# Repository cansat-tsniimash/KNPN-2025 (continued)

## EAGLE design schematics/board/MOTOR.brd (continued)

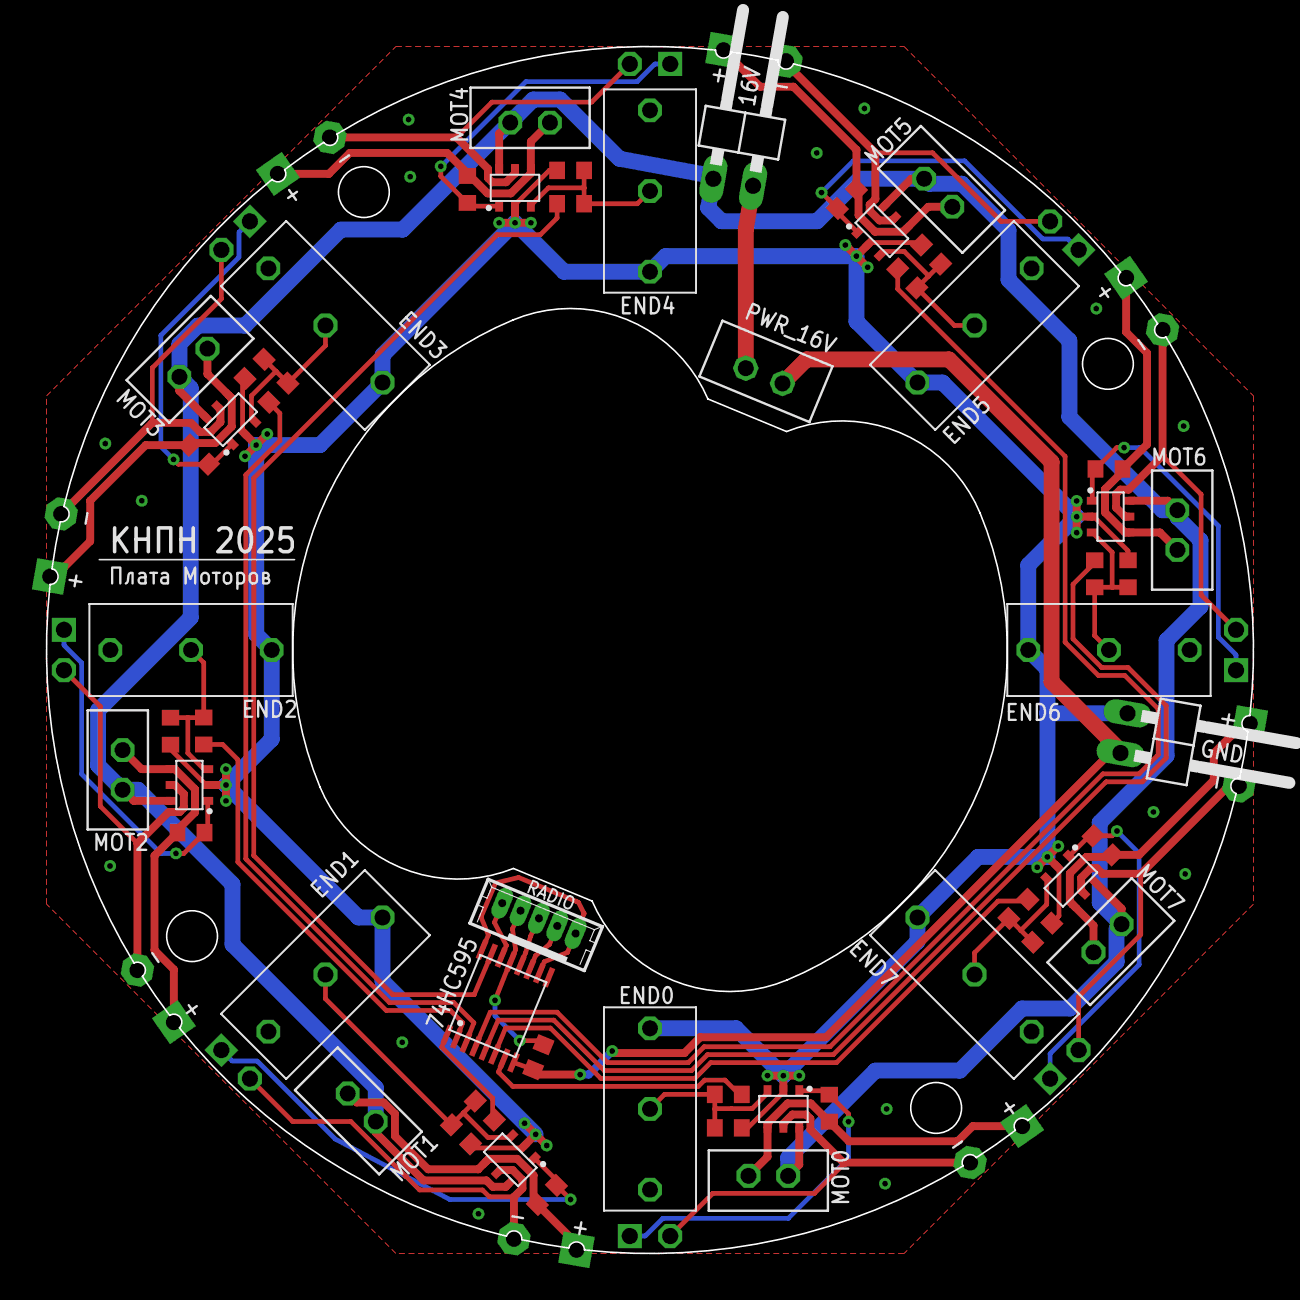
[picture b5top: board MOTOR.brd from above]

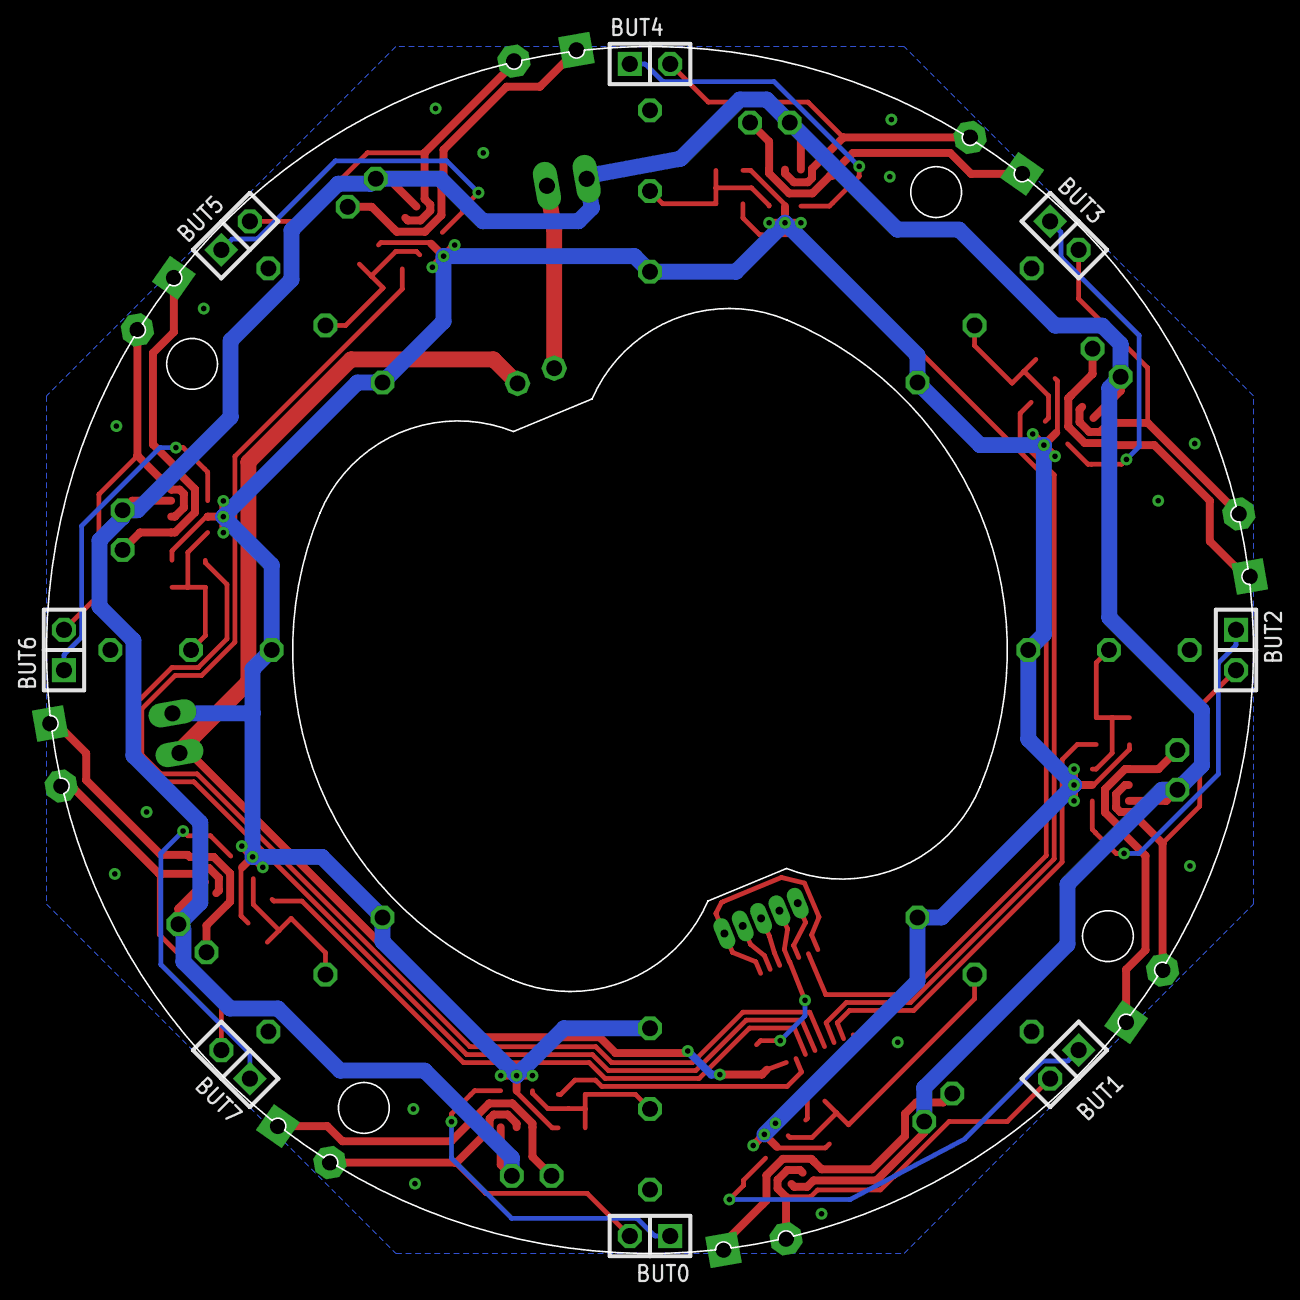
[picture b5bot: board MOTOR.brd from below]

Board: 2 copper layers, 76.0 x 76.0 mm, 71 parts (8 on the bottom side), 49 nets.

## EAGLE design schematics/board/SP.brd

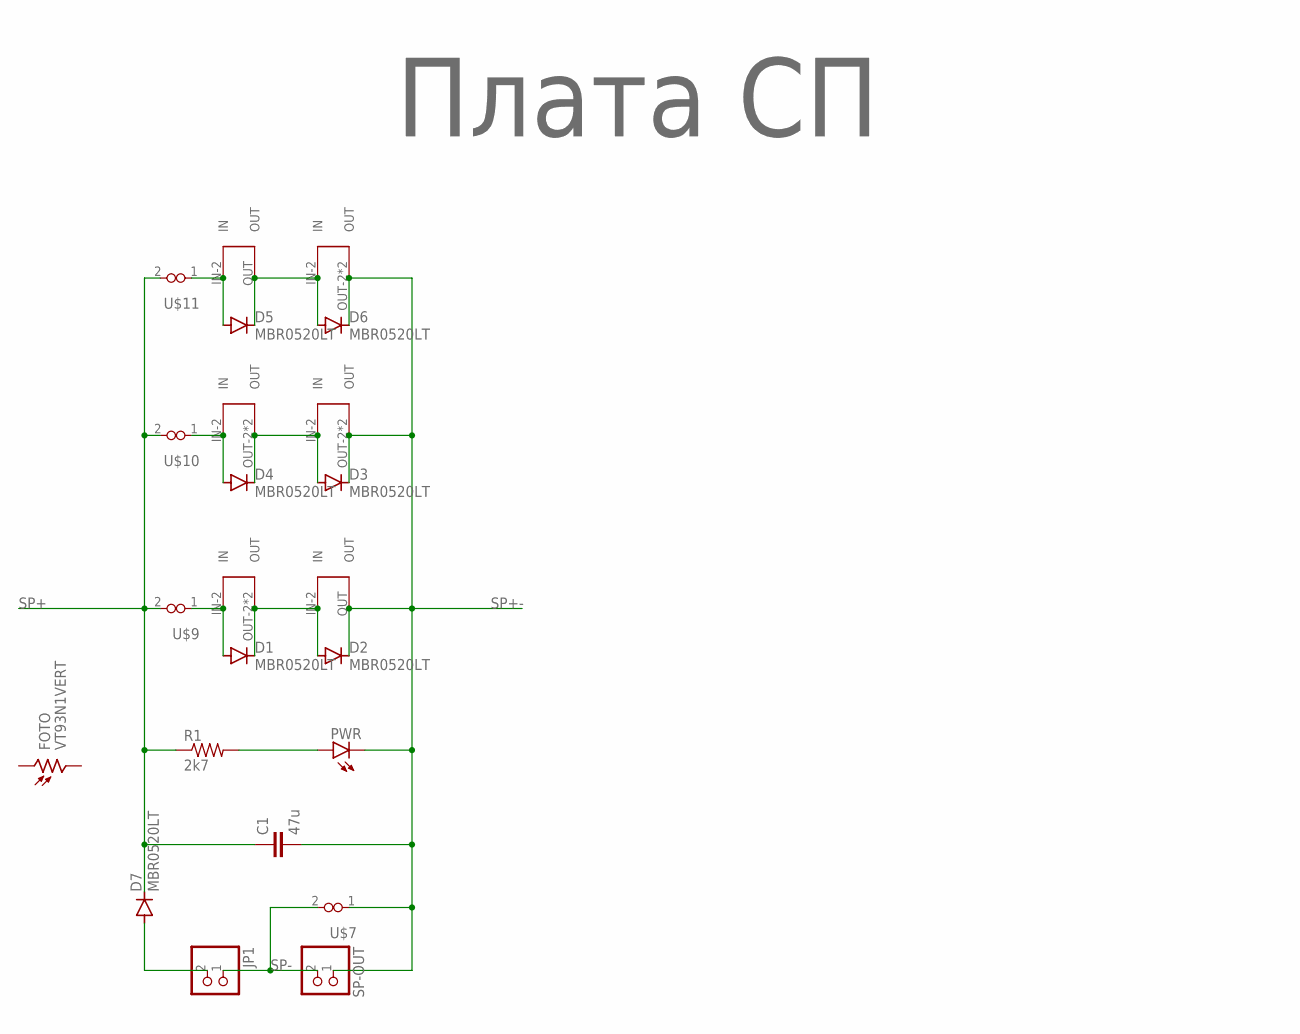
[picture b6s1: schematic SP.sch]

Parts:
C1: 47u; C1210
D1, D2, D3, D4, D5, D6, D7: MBR0520LT; SOD123
FOTO: VT93N1VERT; VT93N1-VERT
JP1: PINHD-1X2; 1X02
PWR: LEDCHIP-LED0603; CHIP-LED0603
R1: 2k7; R0603
SP-OUT: PINHD-1X2; 1X02
U$1, U$3, U$4, U$8: SOLAR-2_INVERT0-2; SOLAR_0-2_INVERT
U$2, U$6: SOLAR-2_INVERT1-2; SOLAR_1-2_INVERT
U$5: Плата СП; LOGO
U$7, U$9, U$10, U$11: VIAS-CONNECT

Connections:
unnamed: D7.A, JP1.2
unnamed: D5.A, U$6.IN-2 (IN), U$11.1
unnamed: D4.A, U$4.IN-2 (IN), U$10.1
unnamed: PWR.A, R1.2
unnamed: D1.C, D2.A, U$1.OUT-2 (OUT), U$1.OUT-21 (OUT), U$2.IN-2 (IN)
unnamed: D3.A, D4.C, U$3.IN-2 (IN), U$4.OUT-2 (OUT), U$4.OUT-21 (OUT)
unnamed: D1.A, U$1.IN-2 (IN), U$9.1
unnamed: D5.C, D6.A, U$6.OUT, U$8.IN-2 (IN)
SP+: C1.1, D7.C, R1.1, U$9.2, U$10.2, U$11.2
SP+-: C1.2, D2.C, D3.C, D6.C, PWR.C, SP-OUT.1, U$2.OUT, U$3.OUT-2 (OUT), U$3.OUT-21 (OUT), U$7.1, U$8.OUT-2 (OUT), U$8.OUT-21 (OUT)
SP-: JP1.1, SP-OUT.2, U$7.2

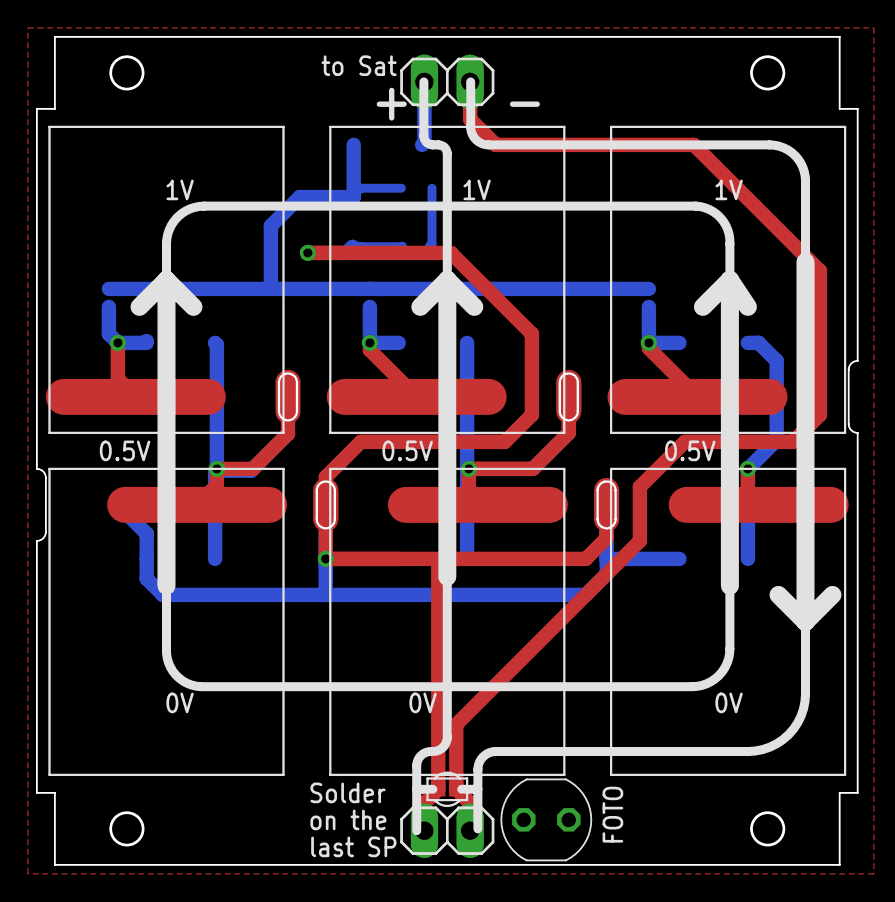
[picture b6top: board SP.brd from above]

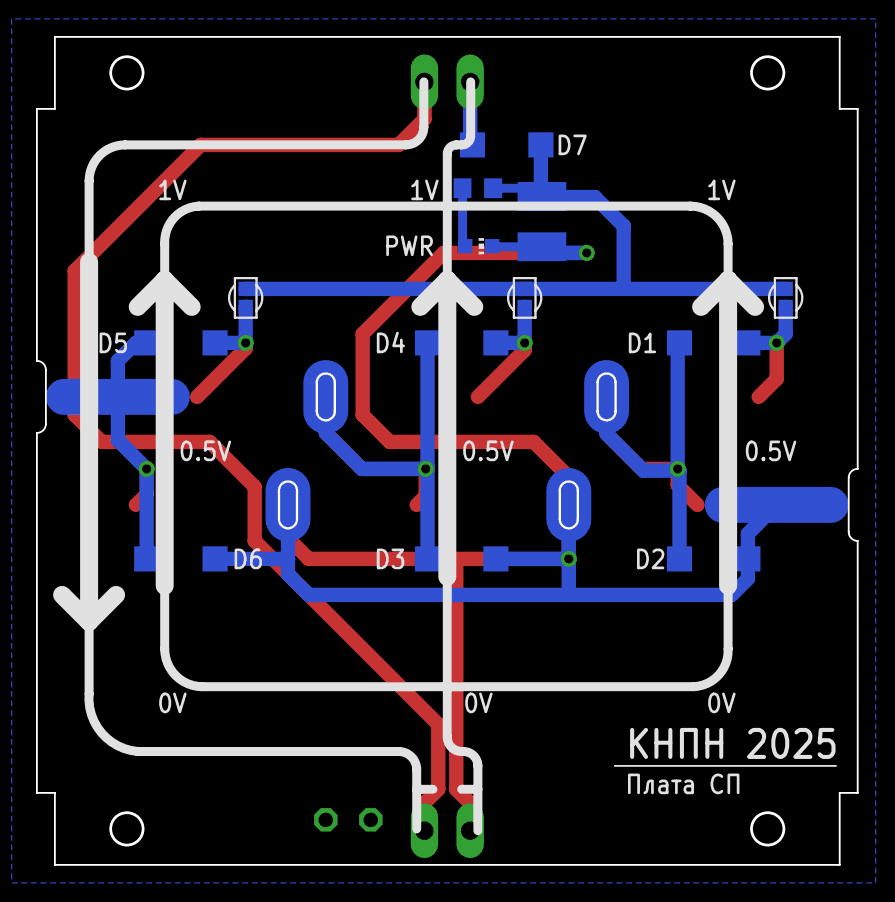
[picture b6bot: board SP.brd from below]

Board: 2 copper layers, 45.5 x 45.9 mm, 24 parts (14 on the bottom side), 11 nets.

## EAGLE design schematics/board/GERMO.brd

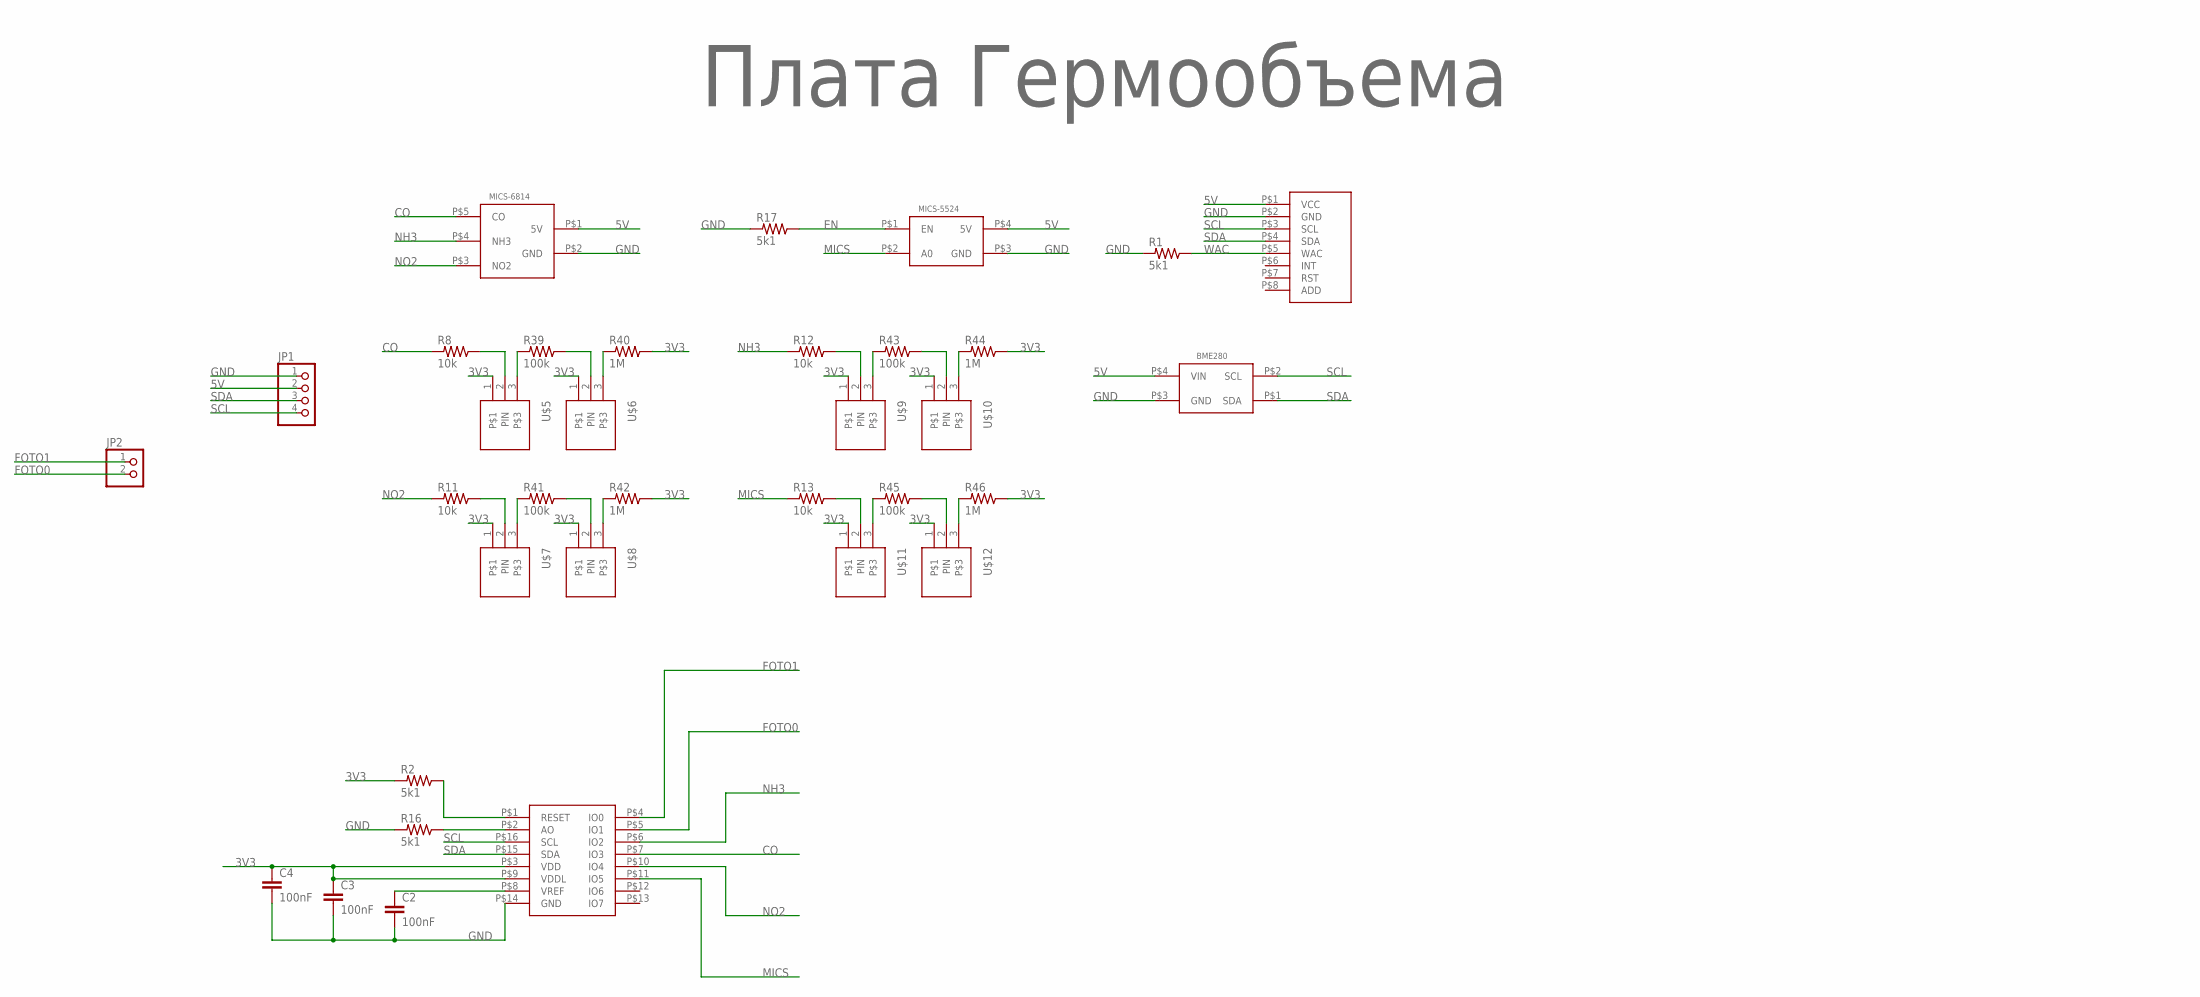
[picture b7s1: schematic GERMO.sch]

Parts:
BME280: BME280BME280-PINS-ONLY; BME280-PINS-ONLY
C2, C3, C4: 100nF; C0603
CCS811: CCS811; CSS811
JP1: PINHD-1X4; 1X04
JP2: PINHD-1X2; 1X02
MICS-5524: MICS_5524; MICS-5524
MICS-6814: MICS-6814
R1, R2, R16, R17: 5k1; R0603
R8, R11, R12, R13: 10k; R0603
R39, R41, R43, R45: 100k; R0603
R40, R42, R44, R46: 1M; R0603
U$2: Плата Гермообъема; LOGO
U$5, U$6, U$7, U$8, U$9, U$10, U$11, U$12: CONNECT_3
U$14: AD5593

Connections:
3V3: C3.1, C4.1, R2.2, R40.1, R42.1, R44.1, R46.1, U$5.1, U$6.1, U$7.1, U$8.1, U$9.1, U$10.1, U$11.1, U$12.1, U$14.P$3 (VDD), U$14.P$9 (VDDL)
5V: BME280.P$4 (VIN), CCS811.P$1 (VCC), JP1.2, MICS-5524.P$4 (5V), MICS-6814.P$1 (5V)
CO: MICS-6814.P$5 (CO), R8.2, U$14.P$7 (IO3)
EN: MICS-5524.P$1 (EN), R17.1
FOTO0: JP2.2, U$14.P$5 (IO1)
FOTO1: JP2.1, U$14.P$4 (IO0)
GND: BME280.P$3 (GND), C2.2, C3.2, C4.2, CCS811.P$2 (GND), JP1.1, MICS-5524.P$3 (GND), MICS-6814.P$2 (GND), R1.2, R16.2, R17.2, U$14.P$14 (GND)
MICS: MICS-5524.P$2 (A0), R13.2, U$14.P$11 (IO5)
unnamed: R39.2, U$5.3
unnamed: R8.1, U$5.2 (PIN)
unnamed: R40.2, U$6.3
unnamed: R39.1, U$6.2 (PIN)
unnamed: R41.2, U$7.3
unnamed: R11.1, U$7.2 (PIN)
unnamed: R42.2, U$8.3
unnamed: R41.1, U$8.2 (PIN)
unnamed: R43.2, U$9.3
unnamed: R12.1, U$9.2 (PIN)
unnamed: R44.2, U$10.3
unnamed: R43.1, U$10.2 (PIN)
unnamed: R45.2, U$11.3
unnamed: R13.1, U$11.2 (PIN)
unnamed: R46.2, U$12.3
unnamed: R45.1, U$12.2 (PIN)
unnamed: C2.1, U$14.P$8 (VREF)
unnamed: R16.1, U$14.P$2 (AO)
unnamed: R2.1, U$14.P$1 (RESET)
NH3: MICS-6814.P$4 (NH3), R12.2, U$14.P$6 (IO2)
NO2: MICS-6814.P$3 (NO2), R11.2, U$14.P$10 (IO4)
SCL: BME280.P$2 (SCL), CCS811.P$3 (SCL), JP1.4, U$14.P$16 (SCL)
SDA: BME280.P$1 (SDA), CCS811.P$4 (SDA), JP1.3, U$14.P$15 (SDA)
WAC: CCS811.P$5 (WAC), R1.1

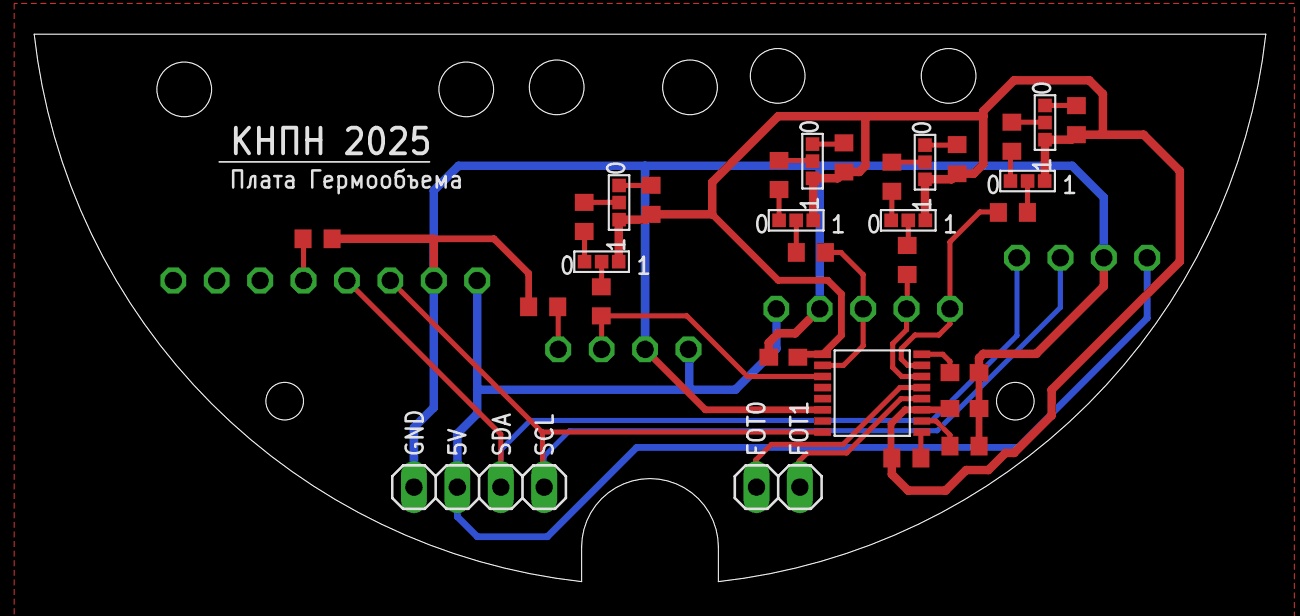
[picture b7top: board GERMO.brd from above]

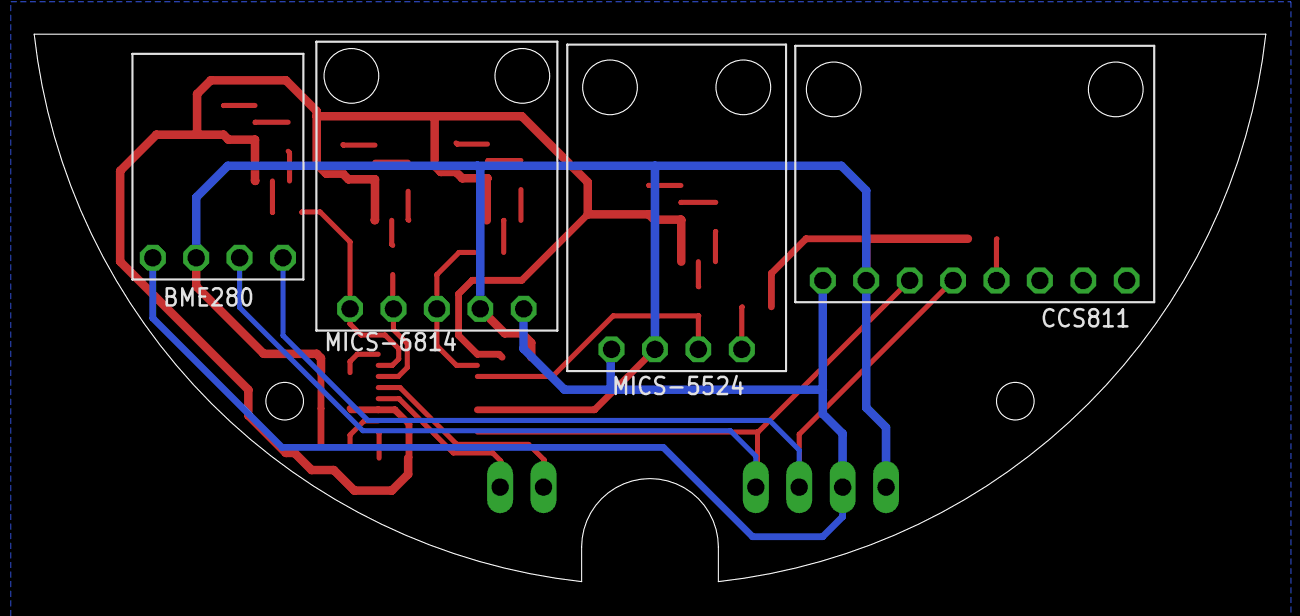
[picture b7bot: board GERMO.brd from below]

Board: 2 copper layers, 72.1 x 32.0 mm, 35 parts (4 on the bottom side), 32 nets.

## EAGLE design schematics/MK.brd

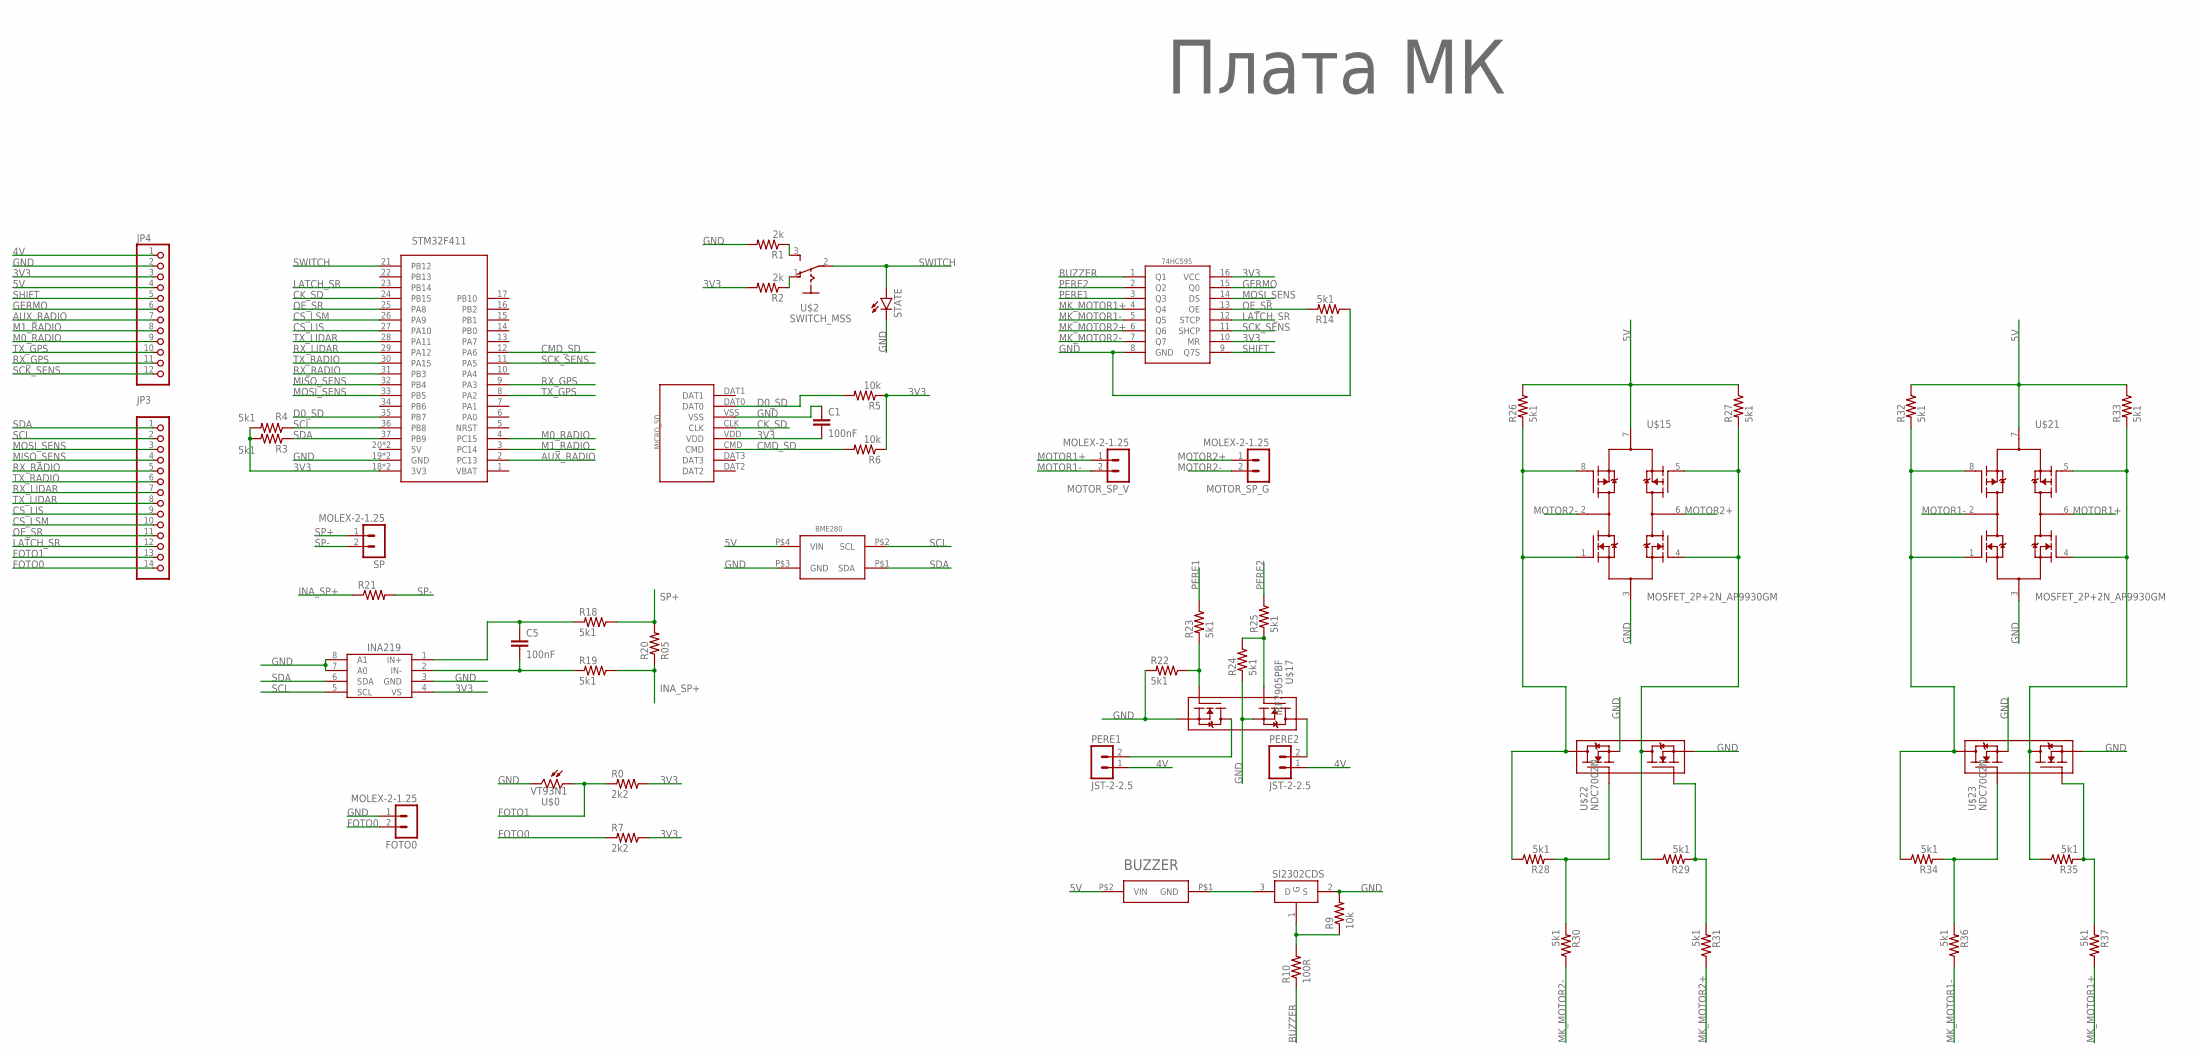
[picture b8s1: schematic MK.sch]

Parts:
BME280: BME280BME280-PINS-ONLY; BME280-PINS-ONLY
BUZZER: BUZZERS8R6; BUZZER-S8R12
C1, C5: 100nF; C0603
FOTO0: MOLEX-2-1.25; 53047-02
JP3: PINHD-1X14; 1X14
JP4: PINHD-1X12; 1X12
MICRO_SD: SD
MOTOR_SP_G: MOLEX-2-1.25; 53047-02
MOTOR_SP_V: MOLEX-2-1.25; 53047-02
PERE1, PERE2: JST-2-2.5
R0, R7: 2k2; R0603
R1, R2: 2k; R0603
R3, R4, R14, R18, R19, R22, R23, R24, R25, R26, R27, R28, R29, R30, R31, R32, R33, R34, R35, R36, R37: 5k1; R0603
R5, R6, R9: 10k; R0603
R10: 100R; R0603
R20: R05; R2512
R21: R-US_0207/15; 0207/15
SI2302CDS: SI2302CDS; SOT23-3
SP: MOLEX-2-1.25; 53047-02
STATE: LEDCHIPLED_0603; CHIPLED_0603
STM32F411: STM32F411_BOARD
U$0: VT93N1
U$1: Плата МК; LOGO
U$2: SWITCH_MSS
U$13: 74HC595; TSSOP16
U$15, U$21: MOSFET_2P+2N_AP9930GM; SO8
U$16: INA219AID; SOT23-8
U$17: IRF7905PBF; SO8
U$22, U$23: NDC7002N; SOT23-6

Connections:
3V3: C1.2, JP4.3, MICRO_SD.VDD, R0.1, R2.2, R3.2, R4.2, R5.1, R6.1, R7.1, STM32F411.18 (3V3), STM32F411.40 (3V3), U$13.10 (MR), U$13.16 (VCC), U$16.4 (VS)
4V: JP4.1, PERE1.1, PERE2.1
5V: BME280.P$4 (VIN), BUZZER.P$2 (VIN), JP4.4, R26.1, R27.1, R32.1, R33.1, U$15.7 (P1P2S), U$21.7 (P1P2S)
AUX_RADIO: JP4.7, STM32F411.2 (PC13)
BUZZER: R10.1, U$13.1 (Q1)
CK_SD: MICRO_SD.CLK, STM32F411.24 (PB15)
CMD_SD: MICRO_SD.CMD, R6.2, STM32F411.12 (PA6)
CS_LIS: JP3.9, STM32F411.27 (PA10)
CS_LSM: JP3.10, STM32F411.26 (PA9)
D0_SD: MICRO_SD.DAT0, R5.2, STM32F411.35 (PB7)
FOTO0: FOTO0.2, JP3.14, R7.2
FOTO1: JP3.13, R0.2, U$0.P$1 (1)
GERMO: JP4.6, U$13.15 (Q0)
GND: BME280.P$3 (GND), C1.1, FOTO0.1, JP4.2, MICRO_SD.VSS, R1.2, R9.2, R14.1, R22.2, R24.2, SI2302CDS.2 (S), STATE.C, STM32F411.19 (GND), STM32F411.39 (GND), U$0.P$2 (2), U$13.8 (GND), U$15.3 (N1N2S), U$16.3 (GND), U$16.7 (A0), U$16.8 (A1), U$17.1 (S2), U$17.3 (S1), U$21.3 (N1N2S), U$22.2 (S2), U$22.5 (S1), U$23.2 (S2), U$23.5 (S1)
INA_SP+: R19.1, R20.1, R21.1
LATCH_SR: JP3.12, STM32F411.23 (PB14), U$13.12 (STCP)
M0_RADIO: JP4.9, STM32F411.4 (PC15)
M1_RADIO: JP4.8, STM32F411.3 (PC14)
MISO_SENS: JP3.4, STM32F411.32 (PB4)
MK_MOTOR1+: R37.1, U$13.4 (Q4)
MK_MOTOR1-: R36.1, U$13.5 (Q5)
MK_MOTOR2+: R31.1, U$13.6 (Q6)
MK_MOTOR2-: R30.1, U$13.7 (Q7)
MOSI_SENS: JP3.3, STM32F411.33 (PB5), U$13.14 (DS)
MOTOR1+: MOTOR_SP_V.1, U$21.6 (P2N2D)
MOTOR1-: MOTOR_SP_V.2, U$21.2 (P1N1D)
MOTOR2+: MOTOR_SP_G.1, U$15.6 (P2N2D)
MOTOR2-: MOTOR_SP_G.2, U$15.2 (P1N1D)
unnamed: R1.1, U$2.3 (S)
unnamed: R2.1, U$2.1 (O)
unnamed: BUZZER.P$1 (GND), SI2302CDS.3 (D)
unnamed: R9.1, R10.2, SI2302CDS.1 (G)
unnamed: C5.2, R19.2, U$16.2 (IN-)
unnamed: C5.1, R18.2, U$16.1 (IN+)
unnamed: PERE1.2, U$17.7 (D2), U$17.8 (D2)
unnamed: PERE2.2, U$17.5 (D1), U$17.6 (D1)
unnamed: R22.1, R23.2, U$17.2 (G2)
unnamed: R24.1, R25.2, U$17.4 (G1)
unnamed: R32.2, R34.1, U$21.1 (N1G), U$21.8 (P1G), U$23.6 (D1)
unnamed: R26.2, R28.1, U$15.1 (N1G), U$15.8 (P1G), U$22.6 (D1)
unnamed: R27.2, R29.1, U$15.4 (N2G), U$15.5 (P2G), U$22.4 (D2)
unnamed: R33.2, R35.1, U$21.4 (N2G), U$21.5 (P2G), U$23.4 (D2)
unnamed: R34.2, R36.2, U$23.1 (G1)
unnamed: R35.2, R37.2, U$23.3 (G2)
unnamed: R28.2, R30.2, U$22.1 (G1)
unnamed: R29.2, R31.2, U$22.3 (G2)
OE_SR: JP3.11, R14.2, STM32F411.25 (PA8), U$13.13 (OE)
PERE1: R23.1, U$13.3 (Q3)
PERE2: R25.1, U$13.2 (Q2)
RX_GPS: JP4.11, STM32F411.9 (PA3)
RX_LIDAR: JP3.7, STM32F411.29 (PA12)
RX_RADIO: JP3.5, STM32F411.31 (PB3)
SCK_SENS: JP4.12, STM32F411.11 (PA5), U$13.11 (SHCP)
SCL: BME280.P$2 (SCL), JP3.2, R4.1, STM32F411.36 (PB8), U$16.5 (SCL)
SDA: BME280.P$1 (SDA), JP3.1, R3.1, STM32F411.37 (PB9), U$16.6 (SDA)
SHIFT: JP4.5, U$13.9 (Q7S)
SP+: R18.1, R20.2, SP.1
SP-: R21.2, SP.2
SWITCH: STATE.A, STM32F411.21 (PB12), U$2.2
TX_GPS: JP4.10, STM32F411.8 (PA2)
TX_LIDAR: JP3.8, STM32F411.28 (PA11)
TX_RADIO: JP3.6, STM32F411.30 (PA15)

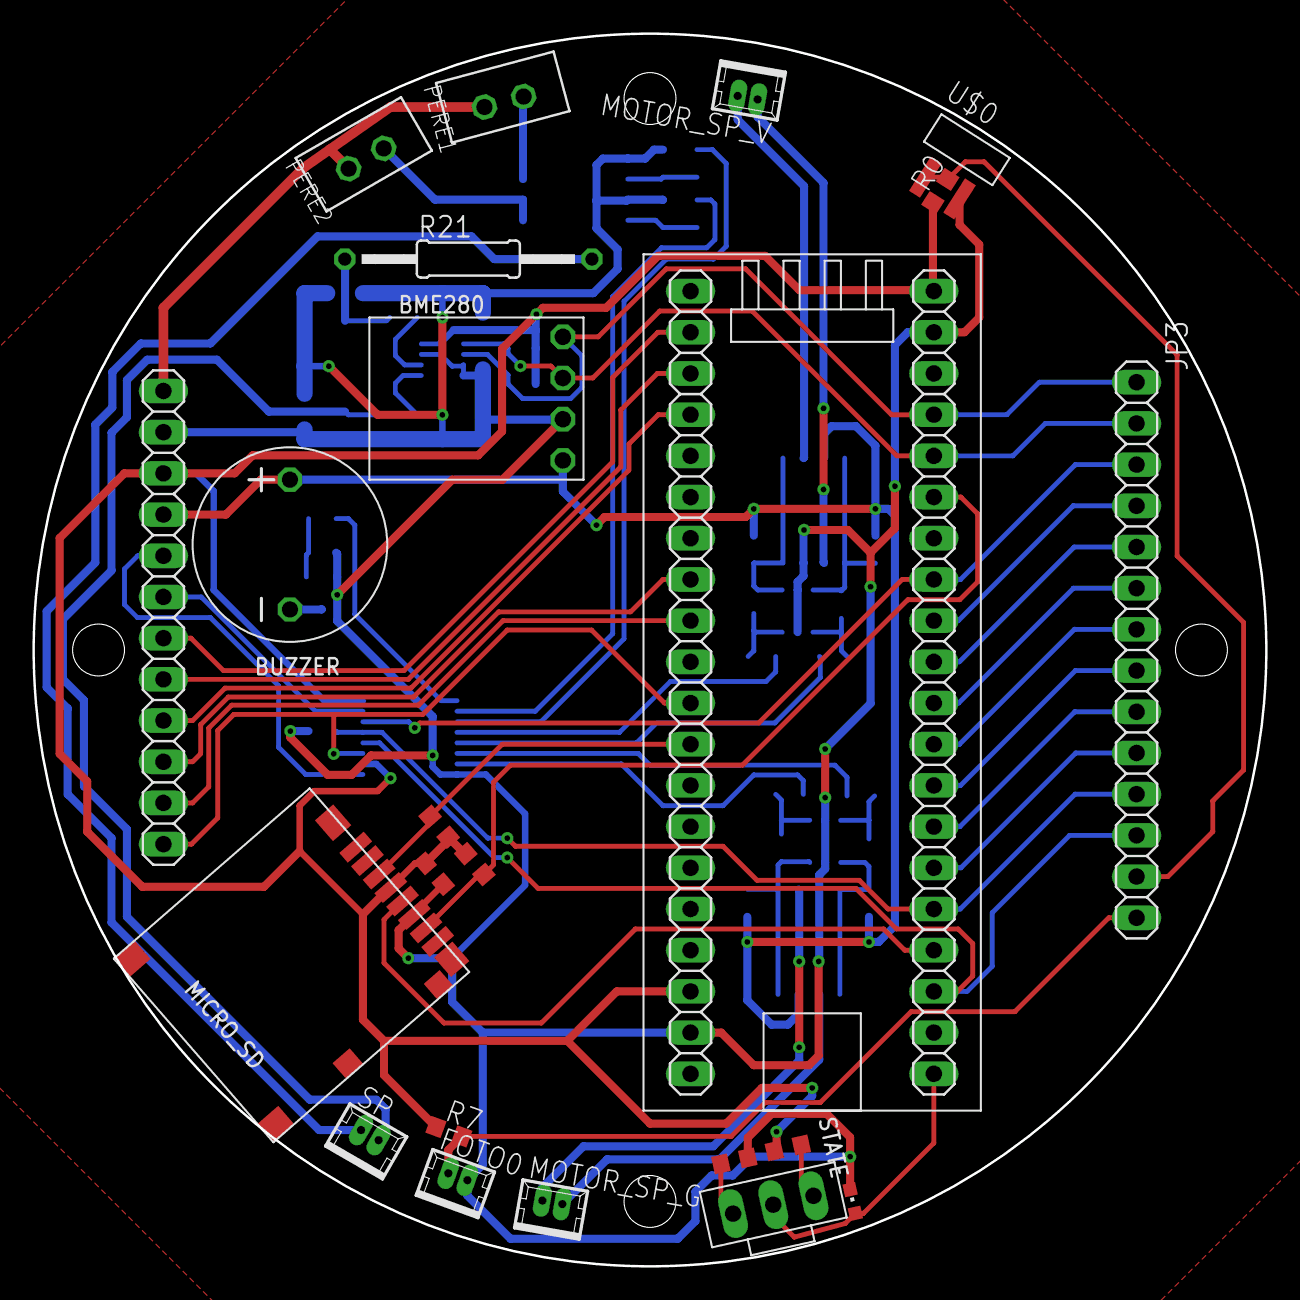
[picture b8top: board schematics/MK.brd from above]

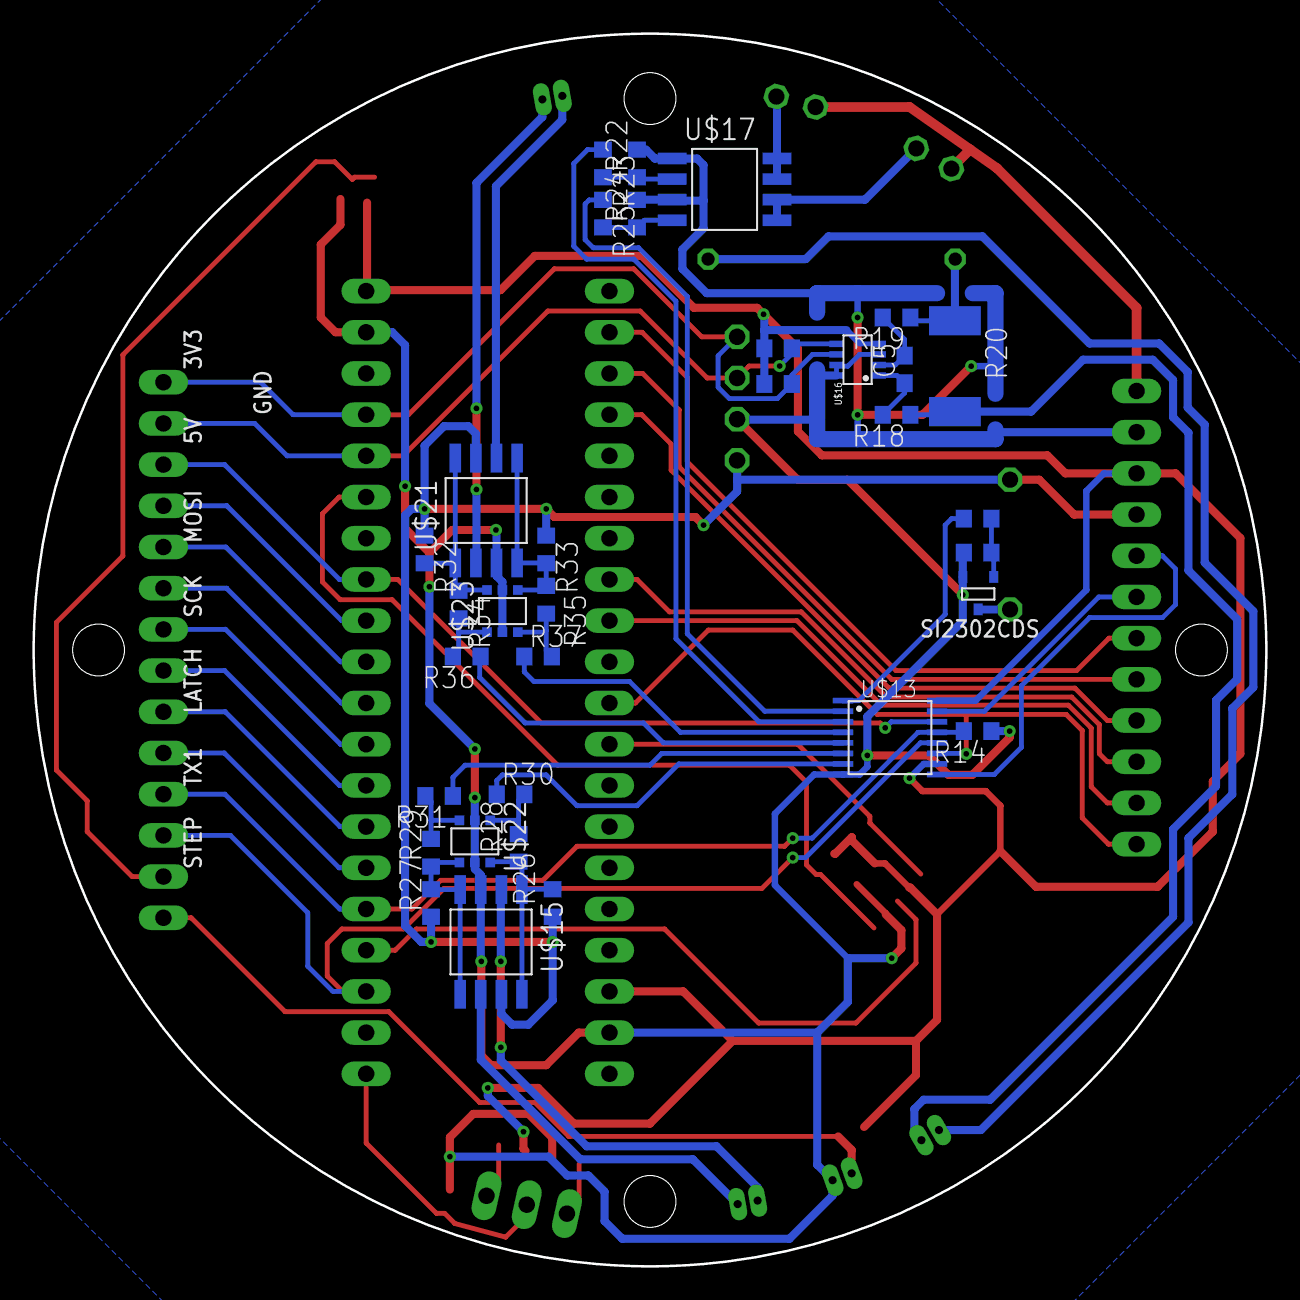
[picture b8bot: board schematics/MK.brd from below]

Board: 2 copper layers, 76.0 x 76.0 mm, 57 parts (33 on the bottom side), 62 nets.

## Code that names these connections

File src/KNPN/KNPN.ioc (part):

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Mcu.Name=STM32F411C(C-E)Ux
Mcu.Package=UFQFPN48
Mcu.UserName=STM32F411CEUx
PA10.Signal=GPIO_Output
PA11.Mode=Asynchronous
PA11.Signal=USART6_TX
PA12.Mode=Asynchronous
PA12.Signal=USART6_RX
PA15.Mode=Asynchronous
PA15.Signal=USART1_TX
PA2.Mode=Asynchronous
PA2.Signal=USART2_TX
PA3.Mode=Asynchronous
PA3.Signal=USART2_RX
PA5.Mode=Full_Duplex_Master
PA5.Signal=SPI1_SCK
PA6.Mode=SD_1_bit
PA6.Signal=SDIO_CMD
PA8.GPIOParameters=PinState,GPIO_Label
PA8.GPIO_Label=OE_SR
PA8.PinState=GPIO_PIN_SET
PA8.Signal=GPIO_Output
PA9.GPIOParameters=PinState
PA9.PinState=GPIO_PIN_SET
PA9.Signal=GPIO_Output
PB0.Signal=GPIO_Output
PB1.Signal=GPIO_Output
PB14.GPIOParameters=GPIO_Label
PB14.GPIO_Label=LATCH_SR
PB14.Signal=GPIO_Output
PB15.Mode=SD_1_bit
PB15.Signal=SDIO_CK
PB3.Mode=Asynchronous
PB3.Signal=USART1_RX
PB4.GPIOParameters=GPIO_PuPd
PB4.GPIO_PuPd=GPIO_NOPULL
PB4.Mode=Full_Duplex_Master
PB4.Signal=SPI1_MISO
PB5.Mode=Full_Duplex_Master
PB5.Signal=SPI1_MOSI
PB7.Mode=SD_1_bit
PB7.Signal=SDIO_D0
PB8.Mode=I2C
PB8.Signal=I2C1_SCL
PB9.Mode=I2C
PB9.Signal=I2C1_SDA
PC14-OSC32_IN.Signal=GPIO_Output
PC15-OSC32_OUT.Signal=GPIO_Output
RCC.HSE_VALUE=25000000
RCC.SYSCLKFreq_VALUE=16000000
board=custom

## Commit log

2024-10-09 буэээ
2024-10-10 Компрессор добавлен
2024-10-10 добавил мотор большой угловой
2024-10-10 старые модельки
2024-10-16 вариант с красивым механизмом
2024-10-17 катуфку сделяль
2024-10-19 Много всякого по моторам
2024-10-19 Моторный рай блин
2024-10-23 Я не могу, это писос, моторы - головняк
2024-10-23 ЗАТЯШКА ПАЧТИ
2024-10-23 возвращение модели катушки
2024-10-26 МегаСвастон, моторный рай растет)
2024-10-27 делаем верх
2024-10-27 исправлены привязки к другим деталям сборки, ВЛАД!!!
2024-10-30 добавлена сборка старой верхней части и плат ВЛ
2024-10-30 мать моя женщина...
2024-10-30 сделаль крепление пережигателя
2024-10-30 гермообъем
2024-11-04 STL для макета
2024-11-05 prt 1 и 2 - держалка для грузиков
2024-11-06 Держалка... для грузиков
2024-11-06 .nbgcxzsd
2024-11-08 Лепестки на печать
2024-11-20 Дальномеры 2 штука
2024-11-20 чототам
2024-11-22 Вау скок всего
2024-11-23 jhgfdd
2024-11-23 Старые платки
2024-11-23 абудаб
2024-11-23 li;egjriughwerip
2024-11-23 добавили все в проект куба
2024-11-28 порядок
2024-11-29 ddddddddddfdddddddde
2024-11-30 радио работает
2024-11-30 ifdhv
2024-12-04 мсчьб
2024-12-04 Больше никогда влад!!!!! я в тг написал
2024-12-06 ПЕРЕИМЕНОВАЛ
2024-12-06 кнопка для моторов
2024-12-06 эщкереееее
2024-12-06 добавл дырдочки
2024-12-07 пам пам тидам
2024-12-07 программа полета
2024-12-07 iyrd
2024-12-07 покрашены детали
2024-12-07 примерили антенну гпс
2024-12-11 Добавил гпс
2024-12-13 mvcmvn fvghjk
2024-12-14 боба
2024-12-14 анимация
2024-12-14 mnkvgf
2024-12-14 сделал видева
2024-12-18 lhiuytrg
2024-12-18 дс дс
2024-12-18 радиомодуль
2024-12-18 lmkbhcgfx
2024-12-18 zxdcbgh
2024-12-18 в процессе видева
2024-12-20 доделал видево
2024-12-20 Платы, скоро будут вырезы
2024-12-20 iokhyte4xsdwbg
2024-12-20 добавлены гпс и дсдс в нашу папку, ВЛАД!!!
2024-12-21 Вырез фоторезистора
2024-12-21 Вырезал почки
2024-12-21 eifugh!
2024-12-21 Андрбша, я тебе покушать принес
2024-12-21 цуар
2024-12-21 масса не тонна, но многовато
2024-12-21 Черттрёё1ёэодцлэощлцв
2024-12-25 ьлтимсчав
2024-12-27 ЧЕРТЁЁЁЁЁЁЁЖОЖУШЧВОУАТ ЦУЩкз
2024-12-27 исправлены ошибки в углах при проектировании конструкции
2025-01-05 для видео
2025-01-05 видео
2025-01-08 /.,mhc
2025-01-09 обновлены видео, добавлена анимация подъема
2025-01-10 Гифки
2025-01-11 добавлены анимации без кромки
2025-01-17 расчет скорости спуска под 7 м/с
2025-01-31 Платки там
2025-01-31 модели маяка и его аккума
2025-01-31 новый гч
2025-02-01 Платы СП 2023
2025-02-01 ПЛАТЫ, АААААААААААААААААААААААААААА
2025-02-01 план-график
2025-02-01 авиполджэъ/ ХПАРОэхжзвапрэ ЖДЛотрипмтсарлншжщлдбьюж
2025-02-05 Затягиватель
2025-02-07 схемы плат
2025-02-07 подготовлены файлы для зимней сессии
2025-02-07 распиновка разъемов плат
2025-02-07 платочки
2025-02-07 длорпамсвч
2025-02-07 разъем в гермообъеме на 8 пинов
2025-02-07 дсдс
2025-02-08 обновлено расположение компонентов на платах
2025-02-09 jhgh
2025-02-12 Расставлены разъемы на плате Радио
2025-02-14 Плата Радио
2025-02-15 цывуа4кеп5рн6го7л8шщ9
2025-02-15 сч мипэхъ\
2025-02-21 Моторчики
2025-02-22 Поправлены платы МК, Радио, Гермо
2025-03-01 лплоав
2025-03-01 схема платы моторов исправлена
2025-03-01 фцыувкаепнргошщз
2025-03-01 компоненты внутри рабочей области
2025-03-02 чёта
2025-03-07 Вроде платы
2025-03-07 Плата MOTOR разведена, но не сделана шелкография
2025-03-07 Покрутили модель, подвигали DC-DC и платы
2025-03-07 проверка плат
2025-03-08 кутиииии
2025-03-08 исправлена отправка пакетов
2025-03-10 Платы готовы
2025-03-10 Че-то с наземкой
2025-03-10 Гыы, мы делаем солнечные панели второй год, гыы...
2025-03-11 Не обижайтесь
2025-03-11 Пу-пу-руу
2025-03-11 заказ плат
2025-03-19 кууутиии продолжение
2025-03-22 ну чёта я сделал и наверное оно работает, но я не уверен
2025-03-26 СД в центре лепестка. Платы версия 2
2025-04-05 /(°_°)\ | |
2025-04-06 написал ccs811
2025-04-11 База и цилиндры для сбросов
2025-04-11 ЛЕПЕСТКИ ВЛАААААД
2025-04-11 Лепестки, основание и крышка подготовлены к печати
2025-04-25 на плате работают бме лис и сд больше там ничего не работает кек
2025-04-25 отверстия в лепестках выше - под высокие межплатные разъемы
2025-04-26 радио
2025-04-26 лсм не работает кек
2025-05-03 наземка + отображалка
2025-05-03 Андрей, после коммита надо пушить!!!!
2025-05-03 Я всё осознал) ещё чуть-чуть отображалки
2025-05-04 Лсм и ацп работают. Хотя в коде ничего и не менялось кек
2025-05-13 авволвадол
2025-05-17 lis и lsm снова работают
2025-05-17 фваывп
2025-05-18 Сборочный чертеж обновлен
2025-05-21 наземка с увеличенным шрифтом
2025-05-21 Работает старое наведение по одной оси. По второй не работает и раскрытие не работает.
2025-05-22 Исравлены отверстия под СБ
2025-05-23 исправил гнпс
2025-05-23 Модель dcdc на 16 В
2025-05-23 Андрей, комп надо выключать и все коммитить!!!!! Уменьшили отверстия в слониках
2025-05-24 яхзчтототампоменял
2025-05-24 деталь для покрытия СП эпоксидкой
2025-05-24 проршлый комит ток новая версия
2025-05-24 правки в наземке
2025-05-28 разрезал базу сп
2025-05-31 Епты гриша
2025-05-31 цварноглждеклуцорйвпАФВПРЛДБГЭЖОПВРАЫФЧЫЛРДПОЖРЭОРОПВЫАФЧЫПРЛОАДПЖНРШГЭ ЖЛДРНГПВАФЧспыЛДЖПНЭГДШНЛГОАПСФвчпырлДЖЭРДЛПОА
2025-06-01 исправлен фоторезистор и шрифты в наземке
2025-06-01 новые детали базы и гермообъема
2025-06-18 Увеличил отверстие под вал двигателя
2025-06-19 нужно делать как нужно, как не нужно делать не нужно
2025-06-24 пепе
2025-06-25 Наземка и лепестки стл
2025-07-04 крайняя версия наземки
2025-07-07 финал
